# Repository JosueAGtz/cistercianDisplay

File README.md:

## Single color Cistercian Display
31 segments digital Cistercian Display with constant current serial to parallel driver. If you need more info please visit my blog https://savageelectronics.com/cistercian-display/

## RGB Cistercian Display
31 Segments RGB Cistercian Display with cascade SK6812 LEDs.

## Cistercian Display Decode

## RGB Cistercian Display Dimensions and Pinout

## Cistercian Display 3D Model

## Cistercian Display Schematic

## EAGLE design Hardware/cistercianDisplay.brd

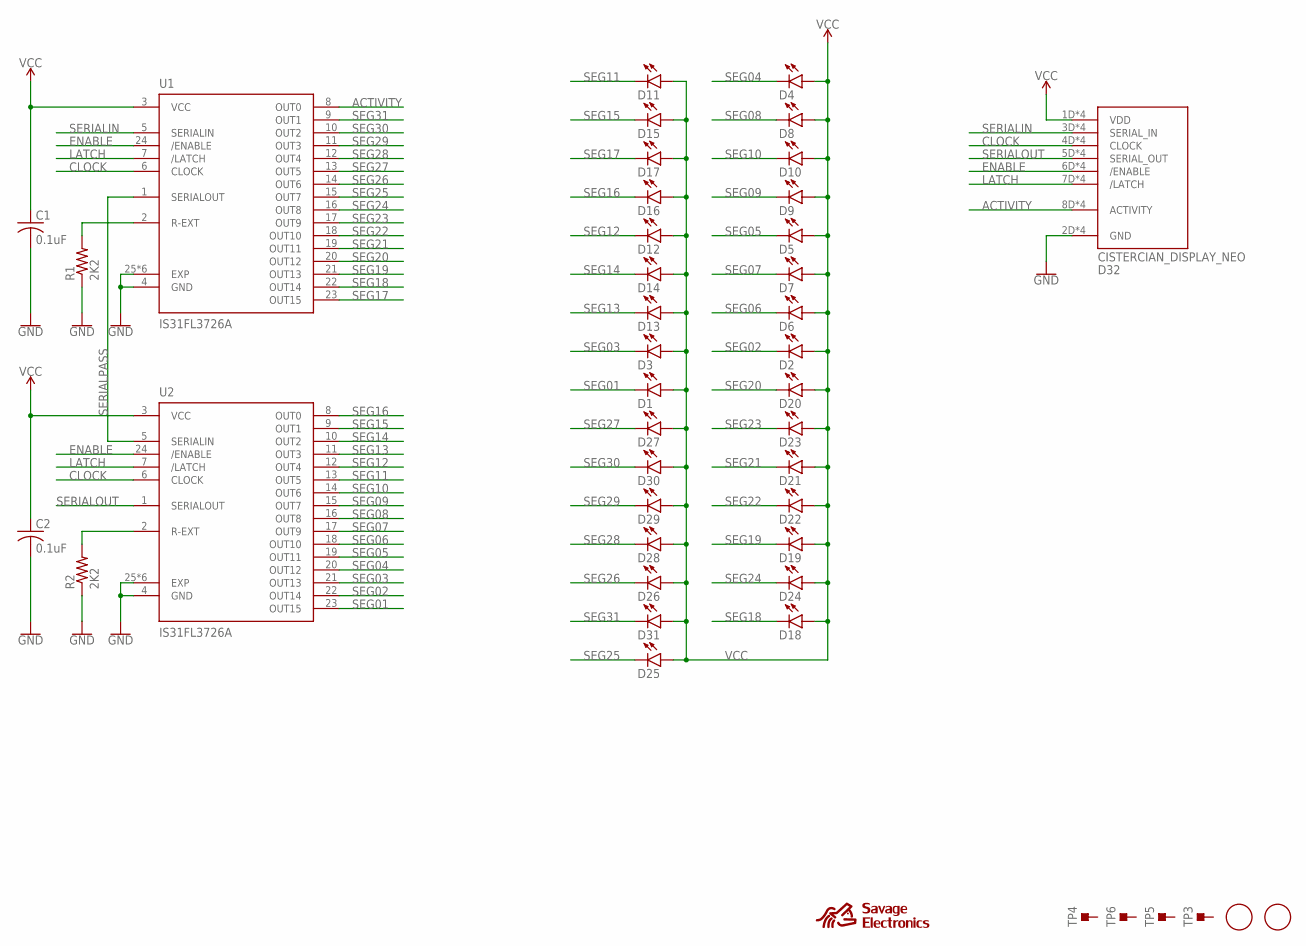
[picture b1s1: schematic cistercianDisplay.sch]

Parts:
C1, C2: 0.1uF; C0603
D1, D2, D3, D4, D5, D6, D7, D8, D9, D10, D11, D12, D13, D14, D15, D16, D17, D18, D19, D20, D21, D22, D23, D24, D25, D26, D27, D28, D29, D30, D31: LEDCHIP-LED0805; CHIP-LED0805
D32: CISTERCIAN_DISPLAY_NEO; CISTERCIAN_DISPLAYNEO
R1, R2: 2K2; R0603
TP3, TP4, TP5, TP6: TESTPOINT_TPS-SMD-10SN; TESTPOINT_SMD-10SN
U1, U2: IS31FL3726A; QFN50P400X400X90-25N
U$1, U$2: FIDUCIAL; FIDUCIAL_1MM
U$3: SE_SMALL_STOP

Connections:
ACTIVITY: D32.8D (ACTIVITY), D32.8DC (ACTIVITY), D32.8U (ACTIVITY), D32.8UC (ACTIVITY), U1.8 (OUT0)
CLOCK: D32.4D (CLOCK), D32.4DC (CLOCK), D32.4U (CLOCK), D32.4UC (CLOCK), U1.6 (CLOCK), U2.6 (CLOCK)
ENABLE: D32.6D (/ENABLE), D32.6DC (/ENABLE), D32.6U (/ENABLE), D32.6UC (/ENABLE), U1.24 (/ENABLE), U2.24 (/ENABLE)
GND: C1.2, C2.2, D32.2D (GND), D32.2DC (GND), D32.2U (GND), D32.2UC (GND), R1.1, R2.1, U1.4 (GND), U1.25 (EXP), U1.P$1 (EXP), U1.P$2 (EXP), U1.P$3 (EXP), U1.P$4 (EXP), U1.P$5 (EXP), U2.4 (GND), U2.25 (EXP), U2.P$1 (EXP), U2.P$2 (EXP), U2.P$3 (EXP), U2.P$4 (EXP), U2.P$5 (EXP)
LATCH: D32.7D (/LATCH), D32.7DC (/LATCH), D32.7U (/LATCH), D32.7UC (/LATCH), U1.7 (/LATCH), U2.7 (/LATCH)
unnamed: R2.2, U2.2 (R-EXT)
unnamed: R1.2, U1.2 (R-EXT)
SEG01: D1.C, U2.23 (OUT15)
SEG02: D2.C, U2.22 (OUT14)
SEG03: D3.C, U2.21 (OUT13)
SEG04: D4.C, U2.20 (OUT12)
SEG05: D5.C, U2.19 (OUT11)
SEG06: D6.C, U2.18 (OUT10)
SEG07: D7.C, U2.17 (OUT9)
SEG08: D8.C, U2.16 (OUT8)
SEG09: D9.C, U2.15 (OUT7)
SEG10: D10.C, U2.14 (OUT6)
SEG11: D11.C, U2.13 (OUT5)
SEG12: D12.C, U2.12 (OUT4)
SEG13: D13.C, U2.11 (OUT3)
SEG14: D14.C, U2.10 (OUT2)
SEG15: D15.C, U2.9 (OUT1)
SEG16: D16.C, U2.8 (OUT0)
SEG17: D17.C, U1.23 (OUT15)
SEG18: D18.C, U1.22 (OUT14)
SEG19: D19.C, U1.21 (OUT13)
SEG20: D20.C, U1.20 (OUT12)
SEG21: D21.C, U1.19 (OUT11)
SEG22: D22.C, U1.18 (OUT10)
SEG23: D23.C, U1.17 (OUT9)
SEG24: D24.C, U1.16 (OUT8)
SEG25: D25.C, U1.15 (OUT7)
SEG26: D26.C, U1.14 (OUT6)
SEG27: D27.C, U1.13 (OUT5)
SEG28: D28.C, U1.12 (OUT4)
SEG29: D29.C, U1.11 (OUT3)
SEG30: D30.C, U1.10 (OUT2)
SEG31: D31.C, U1.9 (OUT1)
SERIALIN: D32.3D (SERIAL_IN), D32.3DC (SERIAL_IN), D32.3U (SERIAL_IN), D32.3UC (SERIAL_IN), U1.5 (SERIALIN)
SERIALOUT: D32.5D (SERIAL_OUT), D32.5DC (SERIAL_OUT), D32.5U (SERIAL_OUT), D32.5UC (SERIAL_OUT), U2.1 (SERIALOUT)
SERIALPASS: U1.1 (SERIALOUT), U2.5 (SERIALIN)
VCC: C1.1, C2.1, D1.A, D2.A, D3.A, D4.A, D5.A, D6.A, D7.A, D8.A, D9.A, D10.A, D11.A, D12.A, D13.A, D14.A, D15.A, D16.A, D17.A, D18.A, D19.A, D20.A, D21.A, D22.A, D23.A, D24.A, D25.A, D26.A, D27.A, D28.A, D29.A, D30.A, D31.A, D32.1D (VDD), D32.1DC (VDD), D32.1U (VDD), D32.1UC (VDD), U1.3 (VCC), U2.3 (VCC)

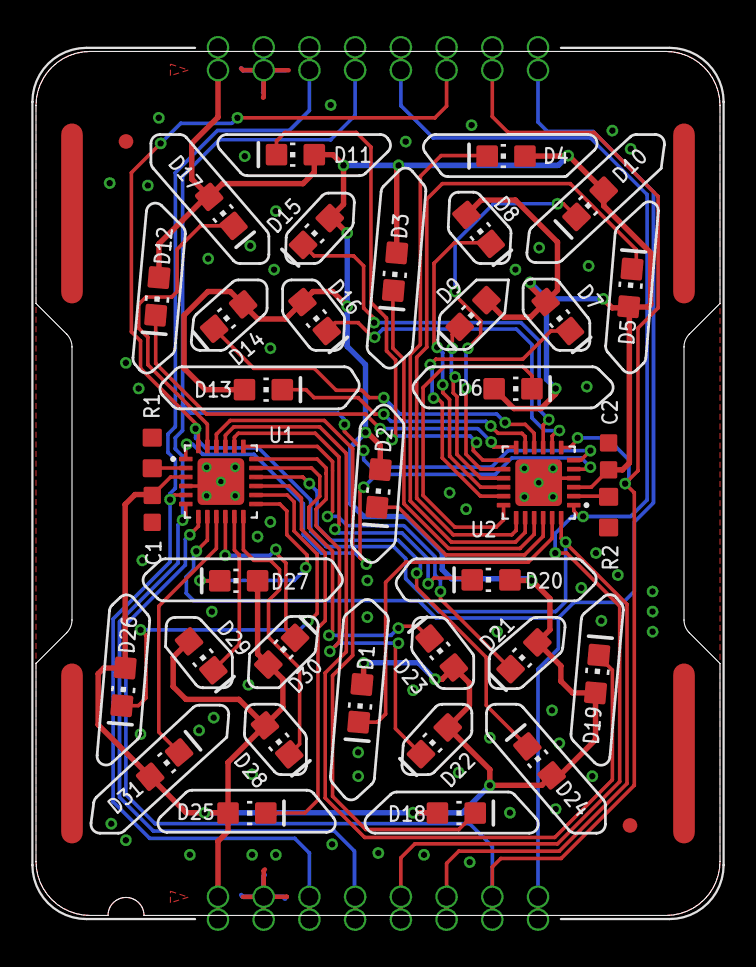
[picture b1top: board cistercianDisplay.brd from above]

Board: 2 copper layers, 38.0 x 48.0 mm, 45 parts (1 on the bottom side), 42 nets.

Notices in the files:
parts and their libraries:
SparkFun-PowerSymbols: Licensing: Creative Commons ShareAlike 4.0 International - https://creativecommons.org/licenses/by-sa/4.0
